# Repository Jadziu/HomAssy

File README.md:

# HomeAssy

***

Starting something new.

***

### SENSOR NODE:

- ESP-01
- SHT21

***

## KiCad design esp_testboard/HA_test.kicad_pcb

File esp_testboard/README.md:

# Test Board for ESP-01

***

Płyta testowa dzięki, której można uruchomić 10 modułów ESP-01 z jednego źródła zasilania.
PCB zostało podzielone na trzy sekcje: 
- SENSOR NODES (5 modułów)
- CONTROL NODES (5 modułów)
- UART

Sekcja UART jest zbiorem wyprowadzeń transmisji szeregowych z wszystkich 10 modułów.

Sekcje SENSOR oraz CONTROL mają osobne zasilanie realizowane przez stabilizatory
napięcia AMS1117-3.3V. Każda z tych sekcji ma osobny włącznik.

W sekcji SENSOR do modułów ESP można podłączyć czujniki lub inne urządzenia z magistralą 
I2C i zasilaniem 3.3V.

W skecji CONTROL zostały wyprowadzone dwa piny GPIO i podłączone diody sygnalizacyjne.

Dla każdego modułu ESP przewidziany jest włącznik.

***

***

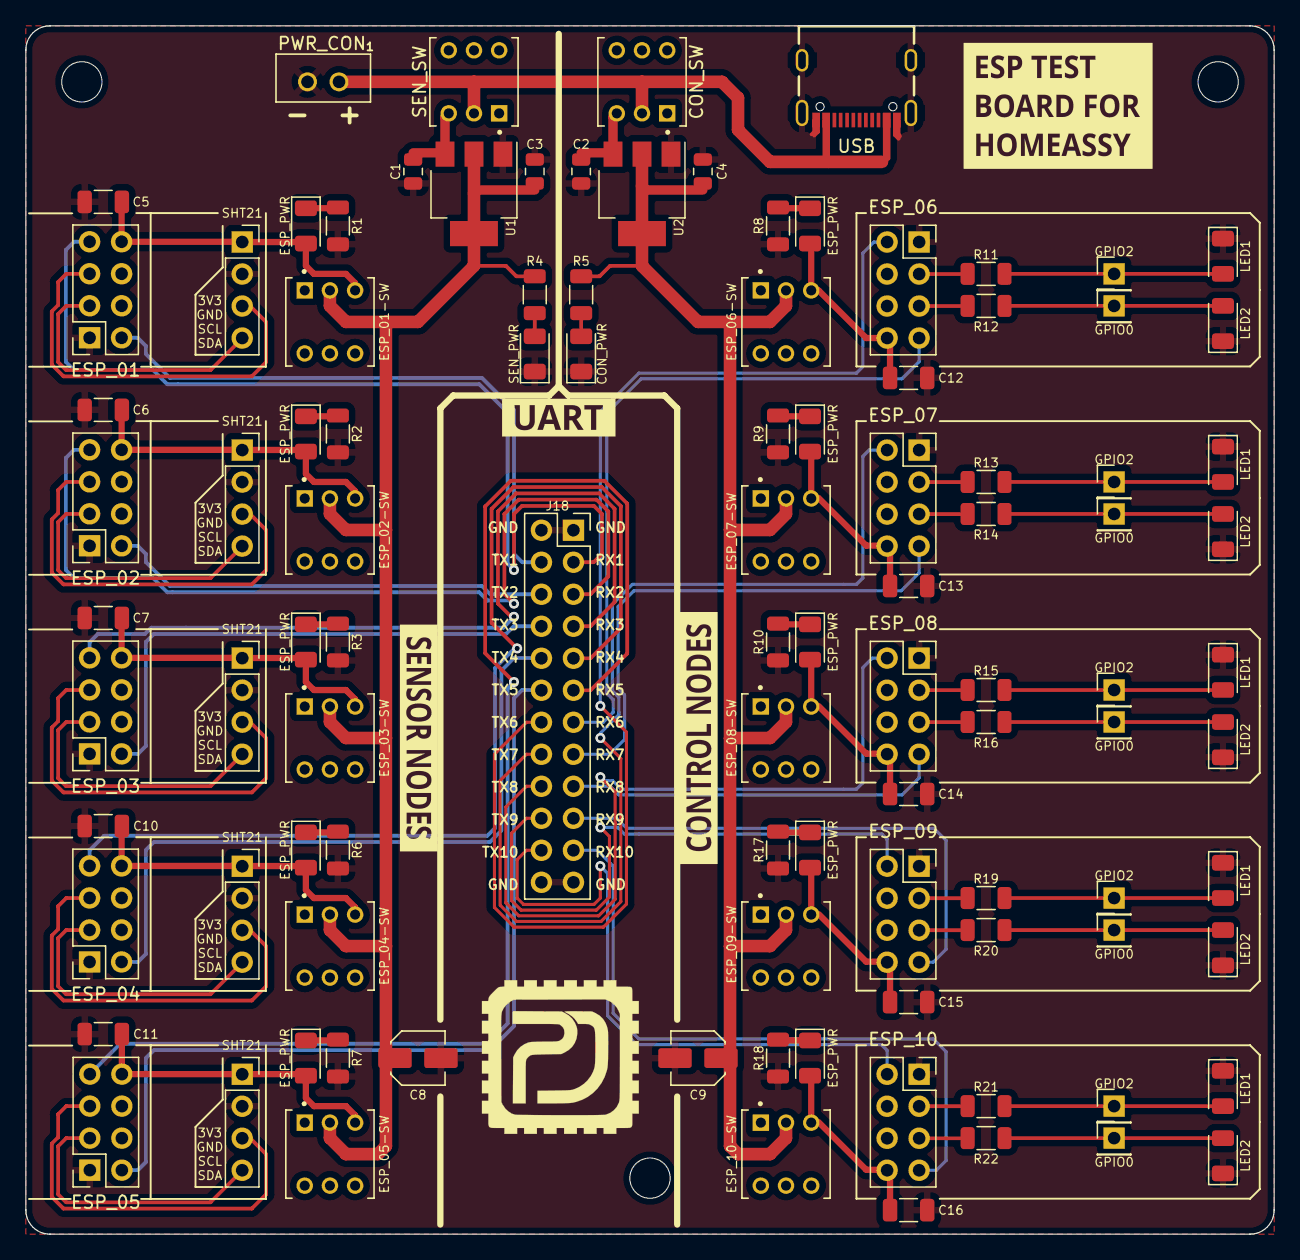
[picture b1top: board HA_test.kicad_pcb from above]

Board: 2 copper layers, 99.1 x 95.9 mm, 107 parts (1 on the bottom side), 78 nets.

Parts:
C1, C2, C3, C4: 10uF; C_0805_2012Metric
C5, C6, C7, C10, C11, C12, C13, C14, C15, C16: 100nF; C_1206_3216Metric
C8, C9: 47uF/6.3V; CAPAE430X550N
CON_PWR: CONTROL_ON; LED_1206_3216Metric
CON_SW: TL2230EEF100; SW_TL2230EEF100
ESP_01, ESP_02, ESP_03, ESP_04, ESP_05, ESP_06, ESP_07, ESP_08, ESP_09, ESP_10: ESP-01; PinSocket_2x04_P2.54mm_Vertical
ESP_01-SW, ESP_02-SW, ESP_03-SW, ESP_04-SW, ESP_05-SW, ESP_06-SW, ESP_07-SW, ESP_08-SW, ESP_09-SW, ESP_10-SW: SW_TL2230EEF100
ESP_PWR: ESP_ON; LED_1206_3216Metric
ESP_PWR#2, ESP_PWR#3, ESP_PWR#4, ESP_PWR#5, ESP_PWR#6, ESP_PWR#7, ESP_PWR#8, ESP_PWR#9, ESP_PWR#10: ESP_ON; LED_1206_3216Metric
GPIO0, GPIO0#2, GPIO0#3, GPIO0#4, GPIO0#5, GPIO2, GPIO2#2, GPIO2#3, GPIO2#4, GPIO2#5: PinHeader_1x01_P2.54mm_Vertical
H1, H2, H3: M3; MountingHole_3.2mm_M3
J18: UART; PinSocket_2x12_P2.54mm_Vertical
LED1, LED1#2, LED1#3, LED1#4, LED1#5: LED1; LED_1206_3216Metric
LED2, LED2#2, LED2#3, LED2#4, LED2#5: LED2; LED_1206_3216Metric
PWR_CON: PWR_IN; 68800211622
R1, R2, R3, R4, R5, R6, R7, R8, R9, R10, R11, R12, R13, R14, R15, R16, R17, R18, R19, R20, R21, R22: 1k; R_1206_3216Metric
Ref**: Val**; PJ_PCB
Ref**#2: Val**; PJ_PCB
SEN_PWR: SENSOR_ON; LED_1206_3216Metric
SEN_SW: TL2230EEF100; SW_TL2230EEF100
SHT21, SHT21#2, SHT21#3, SHT21#4, SHT21#5: SHT21; PinSocket_1x04_P2.54mm_Vertical
U1, U2: AMS1117-3.3; SOT-223-3_TabPin2
USB: 629722000214

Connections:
5V: CON_SW.2, PWR_CON.1, SEN_SW.2, USB.A4 (VBUS), USB.A9 (VBUS1), USB.B4 (VBUS3), USB.B9 (VBUS2)
5VC: C2.1, CON_SW.3, U2.3 (VI)
5VS: C1.1, SEN_SW.3, U1.3 (VI)
GND: C1.2, C2.2, C3.2, C4.2, C5.2, C6.2, C7.2, C8.2, C9.2, C10.2, C11.2, C12.2, C13.2, C14.2, C15.2, C16.2, CON_PWR.1 (K), ESP_01.1, ESP_02.1, ESP_03.1, ESP_04.1, ESP_05.1, ESP_06.1, ESP_07.1, ESP_08.1, ESP_09.1, ESP_10.1, J18.1, J18.2, J18.23, J18.24, LED1.1 (K), LED1#2.1 (K), LED1#3.1 (K), LED1#4.1 (K), LED1#5.1 (K), LED2.1 (K), LED2#2.1 (K), LED2#3.1 (K), LED2#4.1 (K), LED2#5.1 (K), PWR_CON.2, R1.1, R2.1, R3.1, R6.1, R7.1, R8.1, R9.1, R10.1, R17.1, R18.1, SEN_PWR.1 (K), SHT21.2, SHT21#2.2, SHT21#3.2, SHT21#4.2, SHT21#5.2, U1.1 (GND), U2.1 (GND), USB.A1 (GND), USB.A12 (GND1), USB.B1 (GND3), USB.B12 (GND2), USB.S1, USB.S2, USB.S3, USB.S4
unnamed: C5.1, ESP_01.8, ESP_01-SW.3, ESP_PWR#9.2 (A), SHT21.1
unnamed: C6.1, ESP_02.8, ESP_02-SW.3, ESP_PWR#8.2 (A), SHT21#2.1
unnamed: C7.1, ESP_03.8, ESP_03-SW.3, ESP_PWR#7.2 (A), SHT21#3.1
unnamed: C10.1, ESP_04.8, ESP_04-SW.3, ESP_PWR#10.2 (A), SHT21#4.1
unnamed: C11.1, ESP_05.8, ESP_05-SW.3, ESP_PWR#2.2 (A), SHT21#5.1
unnamed: C12.1, ESP_06.8, ESP_06-SW.3, ESP_PWR#4.2 (A)
unnamed: C13.1, ESP_07.8, ESP_07-SW.3, ESP_PWR#3.2 (A)
unnamed: C14.1, ESP_08.8, ESP_08-SW.3, ESP_PWR#5.2 (A)
unnamed: C15.1, ESP_09.8, ESP_09-SW.3, ESP_PWR#6.2 (A)
unnamed: C16.1, ESP_10.8, ESP_10-SW.3, ESP_PWR.2 (A)
unnamed: ESP_PWR#9.1 (K), R1.2
unnamed: ESP_PWR#8.1 (K), R2.2
unnamed: ESP_PWR#7.1 (K), R3.2
unnamed: R4.2, SEN_PWR.2 (A)
unnamed: CON_PWR.2 (A), R5.2
unnamed: ESP_PWR#10.1 (K), R6.2
unnamed: ESP_PWR#2.1 (K), R7.2
unnamed: ESP_PWR#4.1 (K), R8.2
unnamed: ESP_PWR#3.1 (K), R9.2
unnamed: ESP_PWR#5.1 (K), R10.2
unnamed: GPIO2#2.1, LED1.2 (A), R11.2
unnamed: GPIO0#2.1, LED2#2.2 (A), R12.1
unnamed: GPIO2.1, LED1#3.2 (A), R13.2
unnamed: GPIO0#4.1, LED2#5.2 (A), R14.1
unnamed: GPIO2#3.1, LED1#2.2 (A), R15.2
unnamed: GPIO0.1, LED2.2 (A), R16.1
unnamed: ESP_PWR#6.1 (K), R17.2
unnamed: ESP_PWR.1 (K), R18.2
unnamed: GPIO2#4.1, LED1#5.2 (A), R19.2
unnamed: GPIO0#5.1, LED2#4.2 (A), R20.1
unnamed: GPIO2#5.1, LED1#4.2 (A), R21.2
unnamed: GPIO0#3.1, LED2#3.2 (A), R22.1
unnamed: ESP_06.3, R11.1
unnamed: ESP_06.5, R12.2
unnamed: ESP_07.3, R13.1
unnamed: ESP_07.5, R14.2
unnamed: ESP_08.3, R15.1
unnamed: ESP_08.5, R16.2
unnamed: ESP_09.3, R19.1
unnamed: ESP_09.5, R20.2
unnamed: ESP_10.3, R21.1
unnamed: ESP_10.5, R22.2
RX1: ESP_01.7, J18.3
RX2: ESP_02.7, J18.5
RX3: ESP_03.7, J18.7
RX4: ESP_04.7, J18.9
RX5: ESP_05.7, J18.11
RX6: ESP_06.7, J18.13
RX7: ESP_07.7, J18.15
RX8: ESP_08.7, J18.17
RX9: ESP_09.7, J18.19
RX10: ESP_10.7, J18.21
SCL1: ESP_01.5, SHT21.3
SCL2: ESP_02.5, SHT21#2.3
SCL3: ESP_03.5, SHT21#3.3
SCL4: ESP_04.5, SHT21#4.3
SCL5: ESP_05.5, SHT21#5.3
SDA1: ESP_01.3, SHT21.4
SDA2: ESP_02.3, SHT21#2.4
SDA3: ESP_03.3, SHT21#3.4
SDA4: ESP_04.3, SHT21#4.4
SDA5: ESP_05.3, SHT21#5.4
TX1: ESP_01.2, J18.4
TX2: ESP_02.2, J18.6
TX3: ESP_03.2, J18.8
TX4: ESP_04.2, J18.10
TX5: ESP_05.2, J18.12
TX6: ESP_06.2, J18.14
TX7: ESP_07.2, J18.16
TX8: ESP_08.2, J18.18
TX9: ESP_09.2, J18.20
TX10: ESP_10.2, J18.22
VCC1: C3.1, C8.1, ESP_01-SW.2, ESP_02-SW.2, ESP_03-SW.2, ESP_04-SW.2, ESP_05-SW.2, R4.1, U1.2 (VO)
VCC2: C4.1, C9.1, ESP_06-SW.2, ESP_07-SW.2, ESP_08-SW.2, ESP_09-SW.2, ESP_10-SW.2, R5.1, U2.2 (VO)

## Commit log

2022-10-18 README update
2022-10-19 added sensor node; README update
2022-10-23 Major UPDATE
2022-10-23 Main program start.
2022-10-25 sensor_node update; main update
2022-11-06 EVERYTHING CHANGED
2022-11-07 Added publish func to main.py; added subscribe func to esp
2022-11-08 Added third process; changed topic for holiday control
2022-11-15 schematic for ESP tester.
2022-11-16 schematic and PCB for ESP tester
2022-11-22 Micro USB upgraded to USB-C
2022-11-22 Added some libs
2022-11-27 finished test board for ESP
